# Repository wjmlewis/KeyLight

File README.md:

# KeyLight
### A simple keychain light that you can toggle!

## What components are used?
I'm using...
- 1x 555 Timer IC
- 1x 5mm LED
- 2x 47kΩ Resistors
- 1x 220Ω Resistor
- 2x 6mm Push Buttons
- 1x CR2032 Battery Cell Holder
- 1x CR2032 Coin Cell Battery

(you also need a keychain, I've sourced that myself already)

# What does it look like?

### The Schematic

### The PCB Design

### The 3D Model (front and back)

### It Works!

(the GIF may take a sec to load)

## This project was made by me, William (@william on slack) for Hackclub Solder!

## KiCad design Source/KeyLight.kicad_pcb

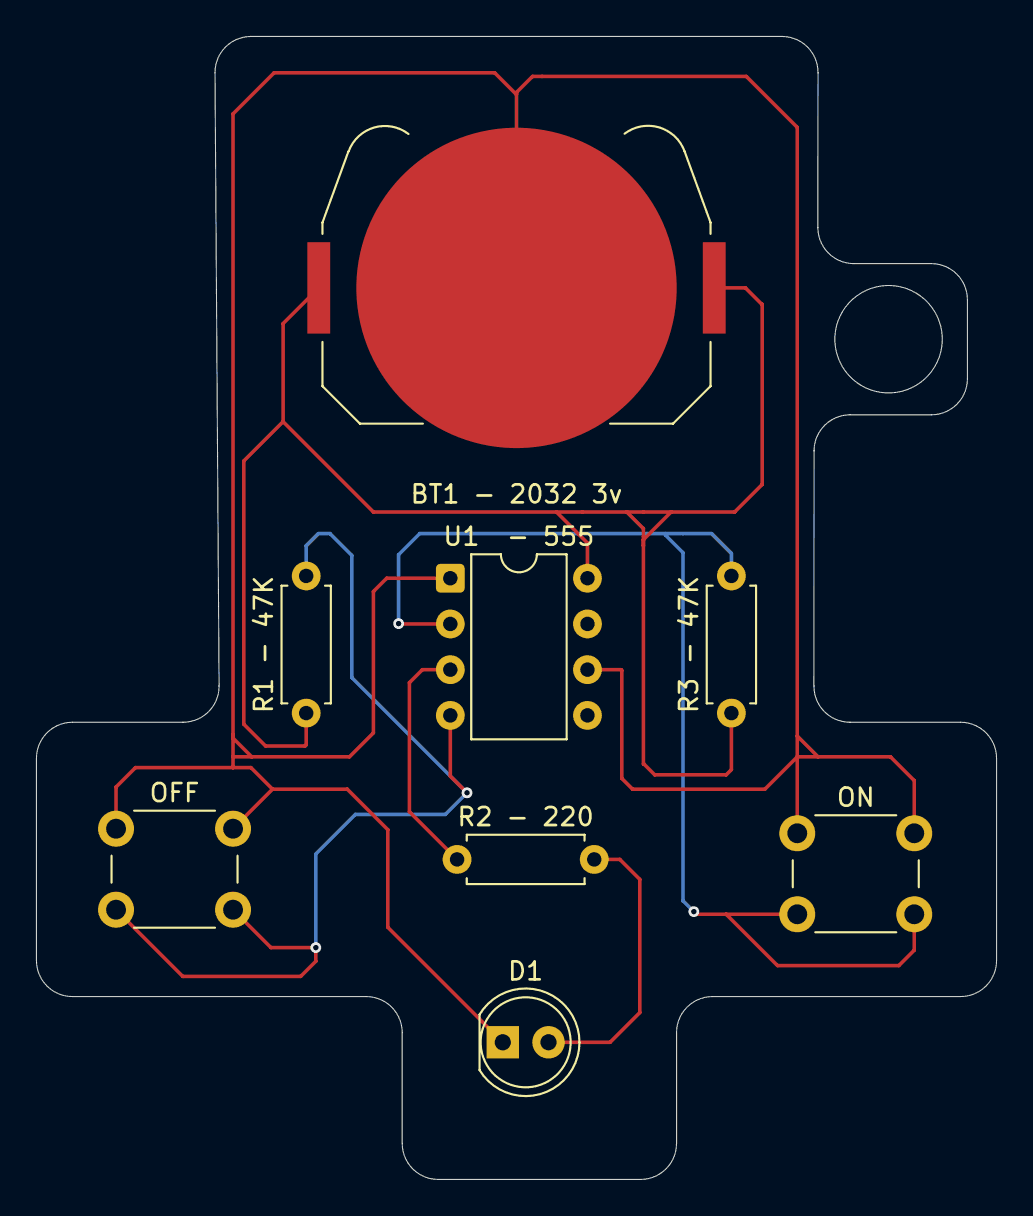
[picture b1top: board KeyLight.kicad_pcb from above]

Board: 2 copper layers, 53.3 x 63.5 mm, 8 parts (0 on the bottom side), 6 nets.

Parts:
BT1 - 2032 3v: Battery_Cell; BatteryHolder_Keystone_3034_1x20mm
D1: LED; LED_D5.0mm
OFF: SW_Push; SW_PUSH_6mm
ON: SW_Push; SW_PUSH_6mm
R1 - 47K, R3 - 47K: R47k; R_Axial_DIN0207_L6.3mm_D2.5mm_P7.62mm_Horizontal
R2 - 220: R220; R_Axial_DIN0207_L6.3mm_D2.5mm_P7.62mm_Horizontal
U1  - 555: ICM7555xP; DIP-8_W7.62mm

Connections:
+3V0: BT1 - 2032 3v.1 (+), R1 - 47K.1, R3 - 47K.1, U1 - 555.8 (VCC)
GND: BT1 - 2032 3v.2 (-), D1.1 (K), OFF.1, ON.1, U1 - 555.1 (GND), U1 - 555.6 (THR)
unnamed: D1.2 (A), R2 - 220.2
unnamed: R2 - 220.1, U1 - 555.3 (Q)
unnamed: OFF.2, R1 - 47K.2, U1 - 555.4 (R)
unnamed: ON.2, R3 - 47K.2, U1 - 555.2 (TR)
